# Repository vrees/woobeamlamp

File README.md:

# woobeamlamp
ESP32 application to control the LEDs of the wood beam lamp

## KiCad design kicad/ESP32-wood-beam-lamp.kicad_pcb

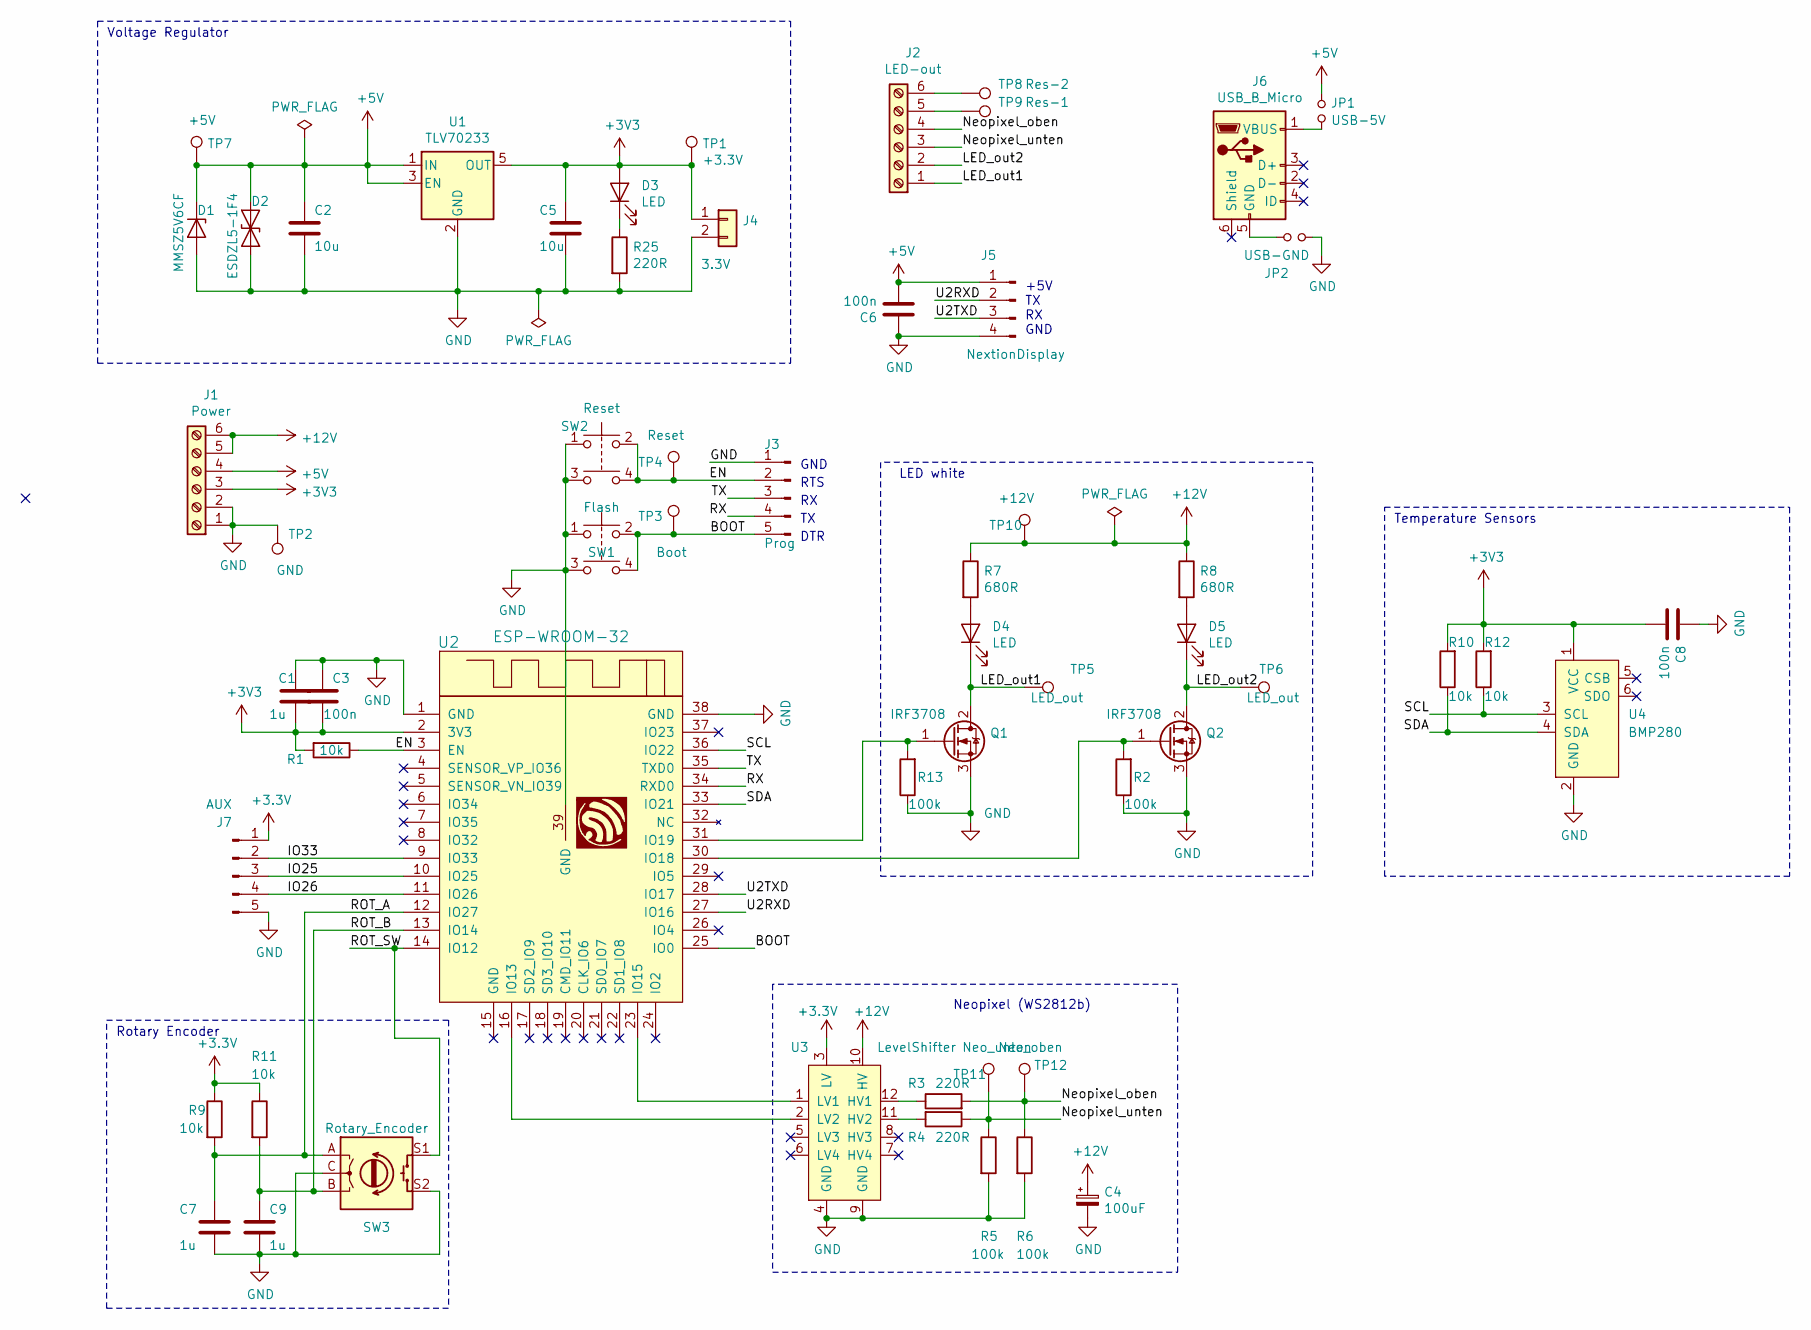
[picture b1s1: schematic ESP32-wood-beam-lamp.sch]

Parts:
C1, C7, C9: 1u; C_1206_3216Metric_Pad1.42x1.75mm_HandSolder
C2, C5: 10u; C_1206_3216Metric_Pad1.42x1.75mm_HandSolder
C3, C6, C8: 100n; C_1206_3216Metric_Pad1.42x1.75mm_HandSolder
C4: 100uF; CP_Radial_D7.5mm_P2.50mm
D1: MMSZ5V6CF; D_SOD-123F
D2: ESDZL5-1F4; D_SOD-323_HandSoldering
D3, D4, D5: LED; LED_1210_3225Metric_Pad1.42x2.65mm_HandSolder
J1: Power; PhoenixContact_MSTBVA_2,5_6-G-5,08_1x06_P5.08mm_Vertical
J2: LED-out; PhoenixContact_MSTBVA_2,5_6-G-5,08_1x06_P5.08mm_Vertical
J3: Prog; PinHeader_1x05_P2.54mm_Vertical
J4: 3.3V; PinHeader_1x02_P2.54mm_Vertical
J5: NextionDisplay; PinHeader_1x04_P2.54mm_Vertical
J6: USB_B_Micro; USB_Micro-B_Molex-105017-0001
J7: AUX; PinHeader_1x05_P2.54mm_Vertical
JP1: USB-5V; PinHeader_1x02_P2.54mm_Vertical
JP2: USB-GND; PinHeader_1x02_P2.54mm_Vertical
Q1, Q2: IRF3708; TO-220-3_Vertical
R1, R9, R10, R11, R12: 10k; R_1206_3216Metric_Pad1.42x1.75mm_HandSolder
R2, R5, R6, R13: 100k; R_1206_3216Metric_Pad1.42x1.75mm_HandSolder
R3, R4, R25: 220R; R_1206_3216Metric_Pad1.42x1.75mm_HandSolder
R7, R8: 680R; R_1206_3216Metric_Pad1.42x1.75mm_HandSolder
SW1: Flash; PCB_PUSH
SW2: Reset; PCB_PUSH
SW3: Rotary_Encoder; RotaryEncoder_Alps_EC11E-Switch_Vertical_H20mm
TP1: +3.3V; TestPoint_Pad_D1.5mm
TP2: GND; TestPoint_Pad_D1.5mm
TP3: Boot; TestPoint_Pad_D1.5mm
TP4: Reset; TestPoint_Pad_D1.5mm
TP5, TP6: LED_out; TestPoint_Pad_D1.5mm
TP7: +5V; TestPoint_Pad_D1.5mm
TP8: Res-2; TestPoint_Pad_D1.5mm
TP9: Res-1; TestPoint_Pad_D1.5mm
TP10: +12V; TestPoint_Pad_D1.5mm
TP11: Neo_unten; TestPoint_Pad_D1.5mm
TP12: Neo_oben; TestPoint_Pad_D1.5mm
U1: TLV70233; SOT-23-5
U2: ESP-WROOM-32; ESP32-WROOM
U3: LevelShifter; DIP-12_W10.16mm_LongPads
U4: BMP280; PinSocket_1x06_P2.54mm_Vertical

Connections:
+5V: C2.1, C6.2, D1.1 (K), D2.1 (A1), J1.4, J5.1, JP1.1, TP7.1, U1.1 (IN), U1.3 (EN); also elsewhere on the board
+12V: C4.1, J1.5, J1.6, R7.1, R8.1, TP10.1, U3.10 (HV); also elsewhere on the board
/BOOT: J3.5, SW1.2, SW1.4, TP3.1, U2.25 (IO0)
/EN: J3.2, R1.1, SW2.2, SW2.4, TP4.1, U2.3 (EN)
/IO25: J7.3, U2.10 (IO25)
/IO26: J7.4, U2.11 (IO26)
/IO33: J7.2, U2.9 (IO33)
/LED_out1: D4.1 (K), J2.1, Q1.2 (D), TP5.1
/LED_out2: D5.1 (K), J2.2, Q2.2 (D), TP6.1
/Neopixel_oben: J2.4, R3.2, R6.1, TP12.1
/Neopixel_unten: J2.3, R4.1, R5.1, TP11.1
/ROT_A: C7.1, R9.2, SW3.A, U2.12 (IO27)
/ROT_B: C9.1, R11.2, SW3.B, U2.13 (IO14)
/ROT_SW: SW3.S1, U2.14 (IO12)
/RX: J3.4, U2.34 (RXD0)
/SCL: R12.1, U2.36 (IO22), U4.3 (SCL)
/SDA: R10.1, U2.33 (IO21), U4.4 (SDA)
/TX: J3.3, U2.35 (TXD0)
/U2RXD: J5.2, U2.27 (IO16)
/U2TXD: J5.3, U2.28 (IO17)
GND: C1.1, C2.2, C3.1, C4.2, C5.2, C6.1, C7.2, C8.1, C9.2, D1.2 (A), D2.2 (A2), J1.1, J1.2, J3.1, J4.2, J5.4, J7.5, JP2.1, Q1.3 (S), Q2.3 (S), R2.1, R5.2, R6.2, R13.1, R25.2, SW1.1, SW1.3, SW2.1, SW2.3, SW3.C, SW3.S2, TP2.1, U1.2 (GND), U2.1 (GND), U2.38 (GND), U2.39 (GND), U3.4 (GND), U3.9 (GND), U4.2 (GND); also elsewhere on the board
unnamed: D3.1 (K), R25.1
unnamed: D4.2 (A), R7.2
unnamed: D5.2 (A), R8.2
unnamed: J2.5, TP9.1
unnamed: J2.6, TP8.1
unnamed: J6.1 (VBUS), JP1.2
unnamed: J6.5 (GND), JP2.2
unnamed: Q1.1 (G), R13.2, U2.31 (IO19)
unnamed: Q2.1 (G), R2.2, U2.30 (IO18)
unnamed: R3.1, U3.12 (HV1)
unnamed: R4.2, U3.11 (HV2)
unnamed: U2.16 (IO13), U3.2 (LV2)
unnamed: U2.23 (IO15), U3.1 (LV1)

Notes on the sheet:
Voltage Regulator
Temperature Sensors
DTR
RTS
GND
+5V TX RX GND
LED white
Neopixel (WS2812b)
Rotary Encoder

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
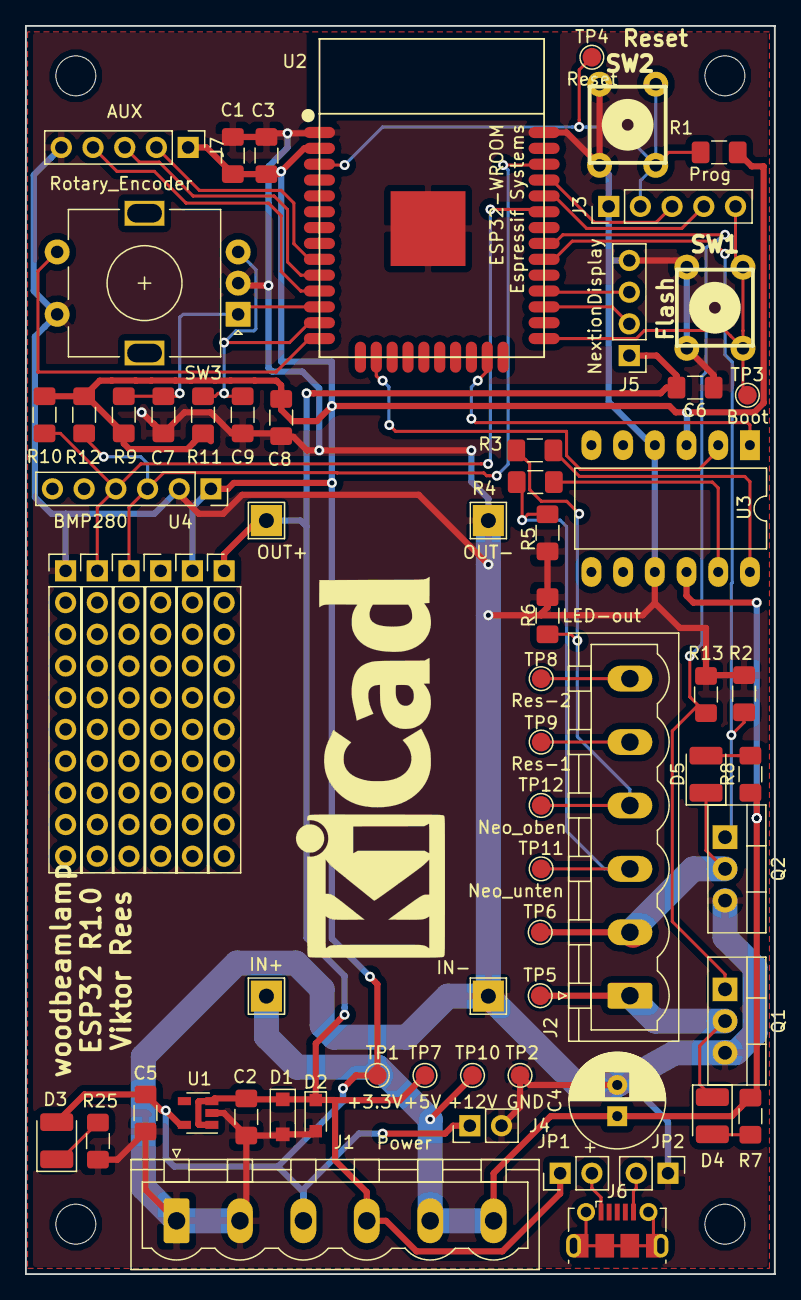
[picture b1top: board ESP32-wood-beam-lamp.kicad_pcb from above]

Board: 2 copper layers, 60.0 x 100.0 mm, 62 parts (0 on the bottom side), 35 nets.

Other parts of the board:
IN+: +12V; TestPoint_THTPad_2.5x2.5mm_Drill1.2mm
IN-: GND; TestPoint_THTPad_2.5x2.5mm_Drill1.2mm
OUT+: +5v; TestPoint_THTPad_2.5x2.5mm_Drill1.2mm
OUT-: GND; TestPoint_THTPad_2.5x2.5mm_Drill1.2mm

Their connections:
+5V: OUT+.1; also elsewhere on the board
+12V: IN+.1; also elsewhere on the board
GND: IN-.1, OUT-.1; also elsewhere on the board

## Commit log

2018-11-04 added BMP280
2018-11-05 datassheet added
2018-11-05 sym-lib uses var now
2018-11-05 Nextion connector added
2018-11-05 IRF3708
2018-11-07 USB Connector added
2018-11-11 footprints added
2018-11-13 rotary Encoder added
2018-11-14 ESP32 footprint added
2018-11-15 rotary
2018-11-16 layout1
2018-11-17 layout2
2018-11-17 Layouting3
2018-11-17 Layouting4
2018-11-18 gerberplot
2018-11-21 WootSpot
2018-11-28 fading
2018-12-26 working fade example
2018-12-28 rotary added
2018-12-30 encoder is done
2018-12-30 all working
2019-01-03 debug color
2020-12-28 .gitignore changed
2020-12-29 Obere weisse Leds funktionieren jetzt. WS2812 Leds ersetzt durch einfache weisse
2020-12-29 adaöpted stepsiize for small values
2023-04-11 Test Github actions calculator
